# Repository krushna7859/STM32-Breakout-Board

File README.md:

# STM32-Breakout-Board

## Design includes:
1) STM32F042K6Tx Processor
2) 16MHz High frequency Oscillator
3) BOOT0 and RESET features
4) USB Type-B Micro power adaptor
5) Serial wire Debugger On-board
6) I2S Protocol
7) Status LED.

### Hopefully you would like this design. This is my first project😇.

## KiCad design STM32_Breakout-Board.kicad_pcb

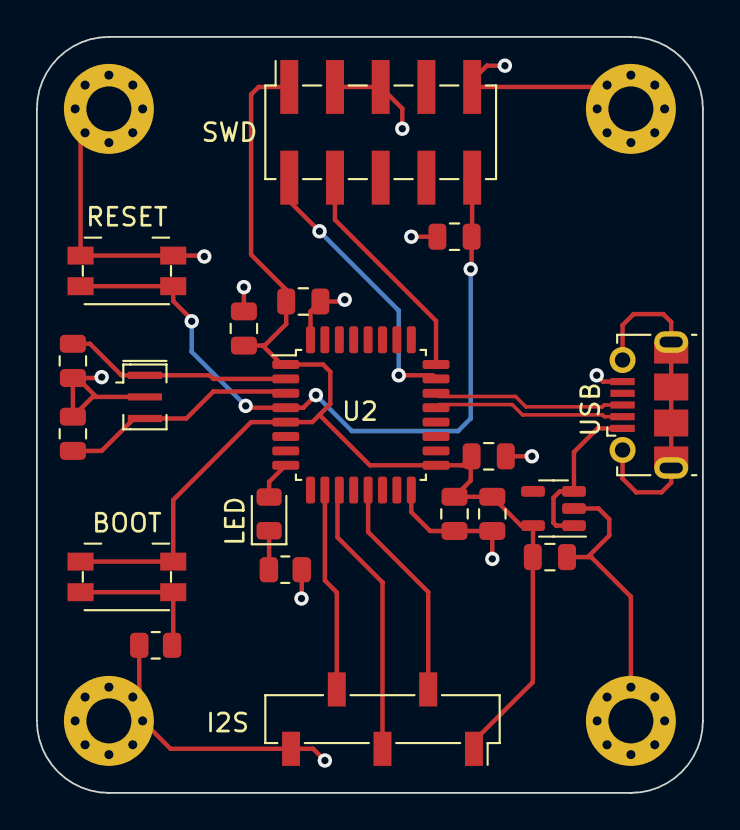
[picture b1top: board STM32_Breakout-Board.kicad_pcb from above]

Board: 2 copper layers, 37.0 x 42.0 mm, 24 parts (0 on the bottom side), 16 nets.

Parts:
BOOT: SW_Push; Panasonic_EVQPUK_EVQPUB
C1: 10nF; C_0805_2012Metric
C2, C8, C9: 1uF; C_0805_2012Metric
C3, C4: 0.1uF; C_0805_2012Metric
C5: 4.7uF; C_0805_2012Metric
C6, C7: 15pF; C_0805_2012Metric
H1, H2, H3, H4: MountingHole_Pad; MountingHole_2.5mm_Pad_Via
I2S: I2S; PinSocket_1x05_P2.54mm_Vertical_SMD_Pin1Right
LED: LED_Small; LED_0805_2012Metric
R1: 10k; R_0805_2012Metric
R2: 220; R_0805_2012Metric
RESET: SW_Push; Panasonic_EVQPUK_EVQPUB
SWD: SWD; PinSocket_2x05_P2.54mm_Vertical_SMD
U1: SPX3819M5-L-3-3; SOT-23-5
U2: STM32F042K6Tx; LQFP-32_7x7mm_P0.8mm
USB: USB_B_Micro; USB_Micro-B_Molex-105017-0001
Y1: 16MHz/10pF; Resonator_SMD_Murata_CSTxExxV-3Pin_3.0x1.1mm

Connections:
+3V3: BOOT.1, C1.1, C2.1, C3.1, C4.1, C5.1, C9.1, I2S.1, SWD.1, U1.5 (OUT), U2.1 (VDD), U2.5 (VDDA), U2.17 (VDDIO2)
+5V: U1.1 (IN), U1.3 (EN), USB.1 (VBUS)
BOOT0: BOOT.2, R1.1
GND: C1.2, C2.2, C3.2, C4.2, C5.2, C6.2, C7.2, C8.2, C9.2, H1.1, H2.1, H3.1, H4.1, I2S.5, R1.2, R2.2, RESET.1, SWD.3, SWD.5, SWD.9, U1.2 (GND), U2.16 (VSS), U2.32 (VSSA), USB.5 (GND), Y1.2
I2S_CK: I2S.3, U2.11 (PA5)
I2S_SD: I2S.2, U2.13 (PA7)
I2S_WS: I2S.4, U2.10 (PA4)
NRST: C8.1, RESET.2, SWD.10, U2.4 (NRST)
unnamed: LED.1 (K), R2.1
unnamed: LED.2 (A), U2.8 (PA2)
OSC_IN: C6.1, U2.2 (PF0), Y1.1
OSC_OUT: C7.1, U2.3 (PF1), Y1.3
SYS_SWCLK: SWD.4, U2.24 (PA14)
SYS_SWDIO: SWD.2, U2.23 (PA13)
USB_D+: U2.22 (PA12), USB.3 (D+)
USB_D-: U2.21 (PA11), USB.2 (D-)
